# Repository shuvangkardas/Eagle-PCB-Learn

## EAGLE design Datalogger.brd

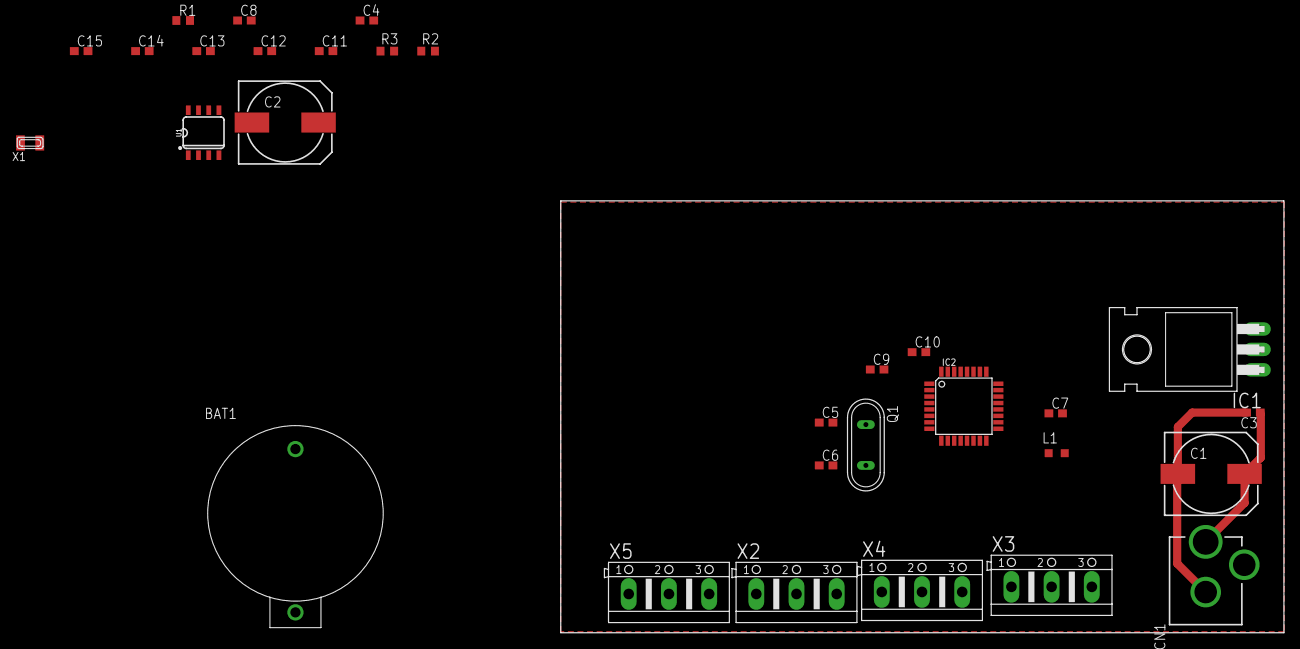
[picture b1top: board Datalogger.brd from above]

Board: 2 copper layers, 90.0 x 53.8 mm, 30 parts (0 on the bottom side), 17 nets.

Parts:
BAT1: BATTERY_1236_C
C1, C2: 100u; 140CLH-1010
C3: 0.1; C0603
C4, C7, C8, C10: 0.1u; C0603
C5, C6: 22p; C0603
C9: 0.01u; C0603
C11, C12, C13, C14, C15: 100nF; C0603
CN1: DCJACK_2MM_PTH
IC1: 7805T; TO220H
IC2: MEGA8-AI; TQFP32-08
L1: 100m; L2012C
Q1: 16M; QS
R1: 10k; R0603
R2, R3: 2.2k; R0603
U1: DS1307Z; SO08-0.15
X1: 32.768KHZ; XTAL3215
X2, X3, X4, X5: AK500/3

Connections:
A0: IC2.23, X2.1
A1: IC2.24, X3.1
A2: IC2.25, X4.1
A3: IC2.26, X5.1
GND: BAT1.-, C1.-, C2.-, C3.2, C4.2, C5.2, C6.2, C7.2, C8.1, C9.2, C10.2, C11.1, C12.1, C13.1, C14.1, C15.1, CN1.GND, IC1.2, IC2.3, IC2.5, IC2.21, U1.4, X2.2, X3.2, X4.2, X5.2
unnamed: C1.+, C3.1, CN1.PWR, IC1.1
unnamed: IC2.29, R1.1
unnamed: C6.1, IC2.8, Q1.2
unnamed: C5.1, IC2.7, Q1.1
unnamed: C7.1, IC2.18, L1.1
unnamed: C8.2, IC2.20
unnamed: BAT1.+, U1.3
unnamed: U1.1, X1.P$2
unnamed: U1.2, X1.P$1
SCL: IC2.28, R3.2, U1.6
SDA: IC2.27, R2.1, U1.5
VCC: C2.+, C4.1, C9.1, C10.1, C11.2, C12.2, C13.2, C14.2, C15.2, IC1.3, IC2.4, IC2.6, L1.2, R1.2, R2.2, R3.1, U1.8, X2.3, X3.3, X4.3, X5.3

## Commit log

2021-07-25 power supply design completed
2021-07-27 microcontroller subcircuit completed
2021-07-28 rtc completed
2021-08-03 pcb design started
2021-08-06 placement started
2021-08-10 ground plane completed
2022-02-23 component value updated

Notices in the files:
parts and their libraries:
SparkFun-Clocks: Licensing: Creative Commons ShareAlike 4.0 International - https://creativecommons.org/licenses/by-sa/4.0
